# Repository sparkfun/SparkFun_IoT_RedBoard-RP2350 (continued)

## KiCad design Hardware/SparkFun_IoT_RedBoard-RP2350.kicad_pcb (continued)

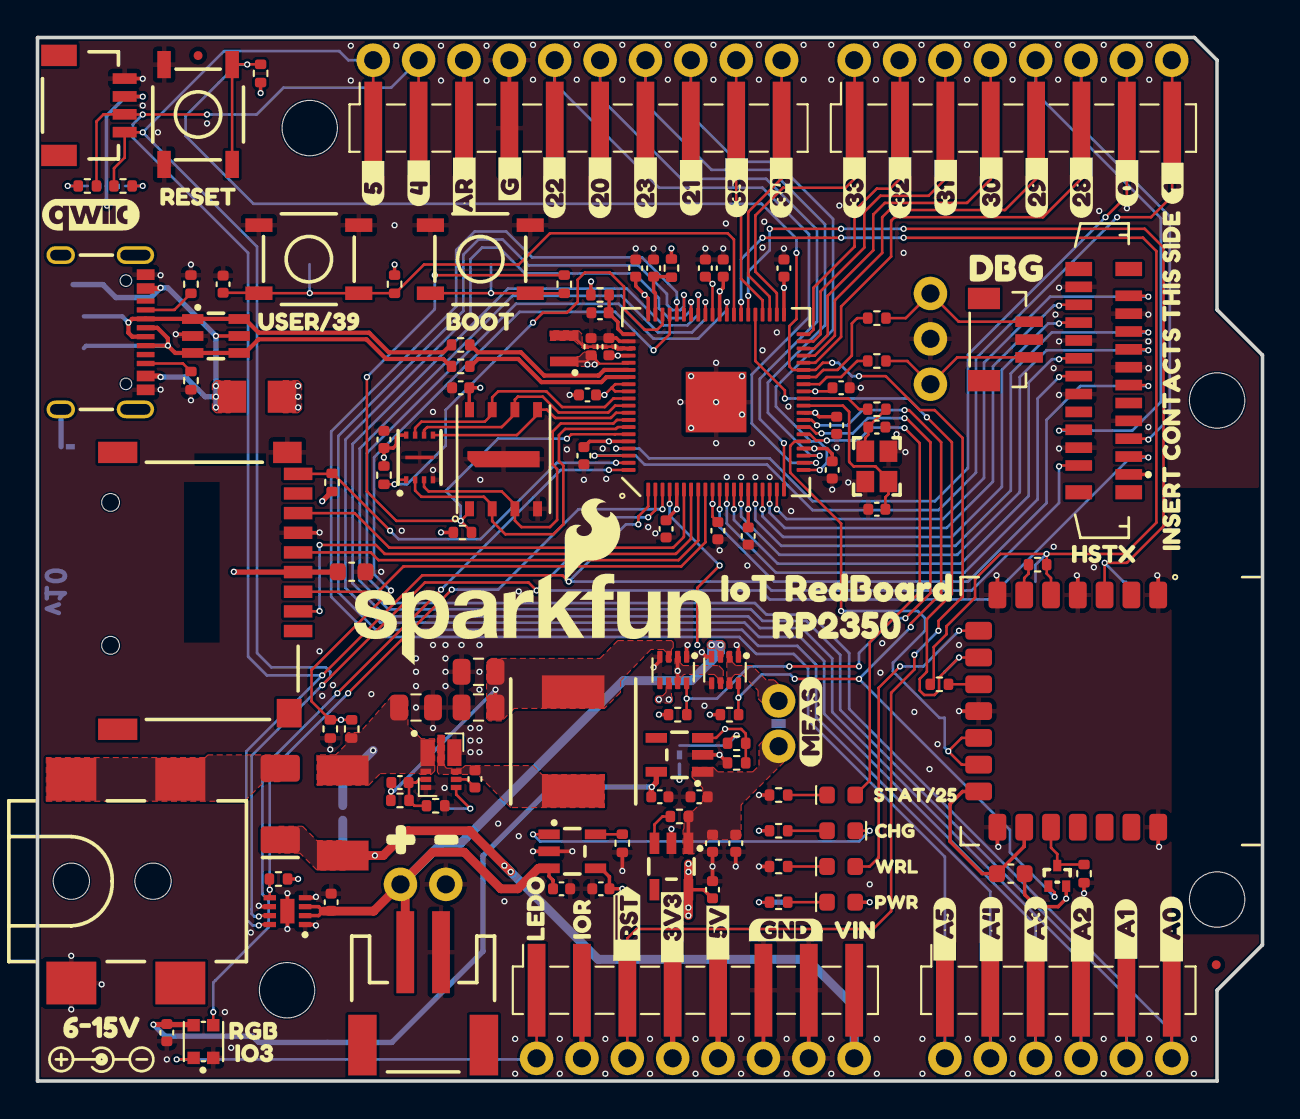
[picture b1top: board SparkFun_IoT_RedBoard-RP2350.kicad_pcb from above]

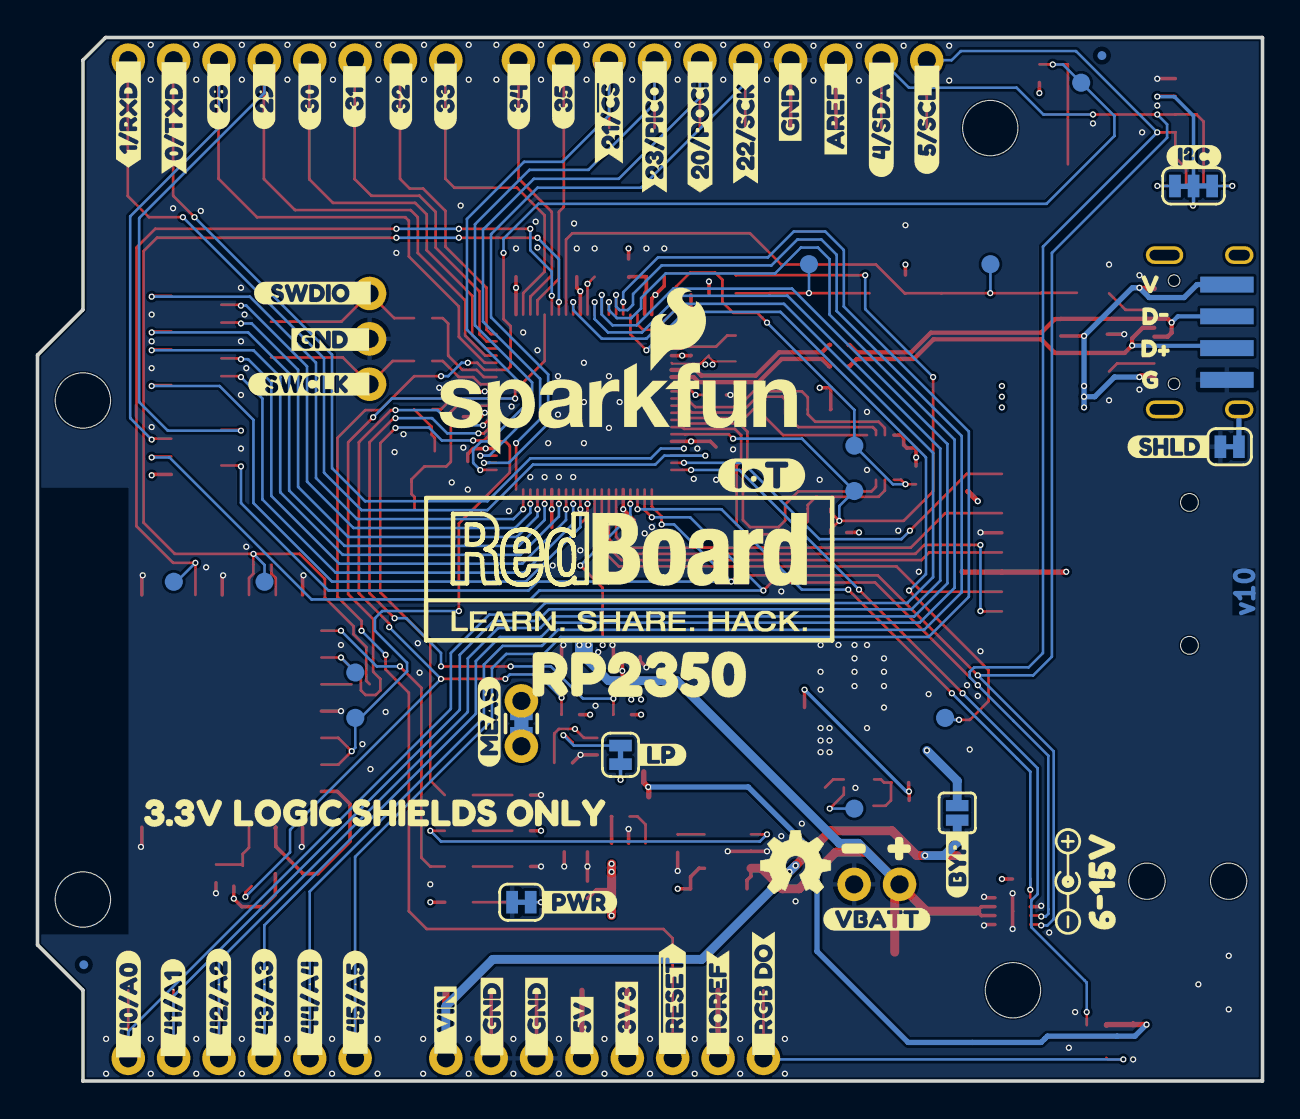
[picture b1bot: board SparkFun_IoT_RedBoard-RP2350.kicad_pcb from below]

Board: 4 copper layers, 68.6 x 58.4 mm, 244 parts (74 on the bottom side), 108 nets.

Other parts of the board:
Ref**: Val**; POLARITY_MARKING_CENTER_POSITIVE
Ref**#2: Val**; OSHW_Logo_4mm
Ref**#3: Val**; POLARITY_MARKING_CENTER_POSITIVE
kibuzzard-67A3E0D1: G***; kibuzzard-67A3E0D1
kibuzzard-67A3E1A1: G***; kibuzzard-67A3E1A1
kibuzzard-67A3E1A7: G***; kibuzzard-67A3E1A7
kibuzzard-67A3E1AE: G***; kibuzzard-67A3E1AE
kibuzzard-67A3E1B5: G***; kibuzzard-67A3E1B5
kibuzzard-67A3E1BE: G***; kibuzzard-67A3E1BE
kibuzzard-67A3E1C5: G***; kibuzzard-67A3E1C5
kibuzzard-67A3E1CD: G***; kibuzzard-67A3E1CD
kibuzzard-67A3E1E0: G***; kibuzzard-67A3E1E0
kibuzzard-67A3E1FA: G***; kibuzzard-67A3E1FA
kibuzzard-67A3E2A5: G***; kibuzzard-67A3E2A5
kibuzzard-67A3E2C6: G***; kibuzzard-67A3E2C6
kibuzzard-67A3E4A3: G***; kibuzzard-67A3E4A3
kibuzzard-67A3E4D1: G***; kibuzzard-67A3E4D1
kibuzzard-67A3E09E: G***; kibuzzard-67A3E09E
kibuzzard-67A3E12A: G***; kibuzzard-67A3E12A
kibuzzard-67A3E17B: G***; kibuzzard-67A3E17B
kibuzzard-67A3E20D: G***; kibuzzard-67A3E20D
kibuzzard-67A3E24D: G***; kibuzzard-67A3E24D
kibuzzard-67A3E25A: G***; kibuzzard-67A3E25A
kibuzzard-67A3E26A: G***; kibuzzard-67A3E26A
kibuzzard-67A3E43C: G***; kibuzzard-67A3E43C
kibuzzard-67A3E45D: G***; kibuzzard-67A3E45D
kibuzzard-67A3E112: G***; kibuzzard-67A3E112
kibuzzard-67A3E140: G***; kibuzzard-67A3E140
kibuzzard-67A3E168: G***; kibuzzard-67A3E168
kibuzzard-67A3E171: G***; kibuzzard-67A3E171
kibuzzard-67A3E183: G***; kibuzzard-67A3E183
kibuzzard-67A3E201: G***; kibuzzard-67A3E201
kibuzzard-67A3E235: G***; kibuzzard-67A3E235
kibuzzard-67A3E254: G***; kibuzzard-67A3E254
kibuzzard-67A3E263: G***; kibuzzard-67A3E263
kibuzzard-67A3E284: G***; kibuzzard-67A3E284
kibuzzard-67A3E455: G***; kibuzzard-67A3E455
kibuzzard-67A3F3F2: G***; kibuzzard-67A3F3F2
kibuzzard-67A3F4AA: G***; kibuzzard-67A3F4AA
kibuzzard-67A3F4E6: G***; kibuzzard-67A3F4E6
kibuzzard-67A3F5C2: G***; kibuzzard-67A3F5C2
kibuzzard-67A3F5D5: G***; kibuzzard-67A3F5D5
kibuzzard-67A3F5FB: G***; kibuzzard-67A3F5FB
kibuzzard-67A3F6A9: G***; kibuzzard-67A3F6A9
kibuzzard-67A3F6CD: G***; kibuzzard-67A3F6CD
kibuzzard-67A3F6E9: G***; kibuzzard-67A3F6E9
kibuzzard-67A3F7A5: G***; kibuzzard-67A3F7A5
kibuzzard-67A3F7B2: G***; kibuzzard-67A3F7B2
kibuzzard-67A3F7C3: G***; kibuzzard-67A3F7C3
kibuzzard-67A3F7D3: G***; kibuzzard-67A3F7D3
kibuzzard-67A3F9C4: G***; kibuzzard-67A3F9C4
kibuzzard-67A3F9DC: G***; kibuzzard-67A3F9DC
kibuzzard-67A3F59C: G***; kibuzzard-67A3F59C
kibuzzard-67A3F62C: G***; kibuzzard-67A3F62C
kibuzzard-67A3F63E: G***; kibuzzard-67A3F63E
kibuzzard-67A3F64D: G***; kibuzzard-67A3F64D
kibuzzard-67A3F71F: G***; kibuzzard-67A3F71F
kibuzzard-67A3F72C: G***; kibuzzard-67A3F72C
kibuzzard-67A3F73E: G***; kibuzzard-67A3F73E
kibuzzard-67A3F74E: G***; kibuzzard-67A3F74E
kibuzzard-67A3F78A: G***; kibuzzard-67A3F78A
kibuzzard-67A3F532: G***; kibuzzard-67A3F532
kibuzzard-67A3F552: G***; kibuzzard-67A3F552
kibuzzard-67A3F565: G***; kibuzzard-67A3F565
kibuzzard-67A3F577: G***; kibuzzard-67A3F577
kibuzzard-67A3F625: G***; kibuzzard-67A3F625
kibuzzard-67A3F633: G***; kibuzzard-67A3F633
kibuzzard-67A3F639: G***; kibuzzard-67A3F639
kibuzzard-67A3F646: G***; kibuzzard-67A3F646
kibuzzard-67A3F657: G***; kibuzzard-67A3F657
kibuzzard-67A3F666: G***; kibuzzard-67A3F666
kibuzzard-67A3F682: G***; kibuzzard-67A3F682
kibuzzard-67A3F699: G***; kibuzzard-67A3F699
kibuzzard-67A3F769: G***; kibuzzard-67A3F769
kibuzzard-67A3F773: G***; kibuzzard-67A3F773
kibuzzard-67A3F799: G***; kibuzzard-67A3F799
kibuzzard-67A657F3: G***; kibuzzard-67A657F3
kibuzzard-67A657FD: G***; kibuzzard-67A657FD
kibuzzard-6761DE89: G***; kibuzzard-6761DE89
kibuzzard-6761DE91: G***; kibuzzard-6761DE91
kibuzzard-6765AF34: G***; kibuzzard-6765AF34
kibuzzard-6765AF51: G***; kibuzzard-6765AF51
kibuzzard-6765B674: G***; kibuzzard-6765B674
kibuzzard-67608A8F: G***; kibuzzard-67608A8F
kibuzzard-67608A60: G***; kibuzzard-67608A60
kibuzzard-67608A88: G***; kibuzzard-67608A88
kibuzzard-67608AA5: G***; kibuzzard-67608AA5
kibuzzard-67608E95: G***; kibuzzard-67608E95
kibuzzard-67608F94: G***; kibuzzard-67608F94
kibuzzard-675766BF: G***; kibuzzard-675766BF
kibuzzard-676080F0: G***; kibuzzard-676080F0
kibuzzard-676083AD, kibuzzard-676083AD#2: G***; kibuzzard-676083AD
kibuzzard-676084E8: G***; kibuzzard-676084E8
kibuzzard-676098CD: G***; kibuzzard-676098CD
kibuzzard-6760897E: G***; kibuzzard-6760897E
kibuzzard-67576710: G***; kibuzzard-67576710
kibuzzard-67576718: G***; kibuzzard-67576718
kibuzzard-67608476: G***; kibuzzard-67608476
kibuzzard-67608507: G***; kibuzzard-67608507
kibuzzard-67608599: G***; kibuzzard-67608599
kibuzzard-67608612: G***; kibuzzard-67608612
kibuzzard-67608662: G***; kibuzzard-67608662
kibuzzard-67608910: G***; kibuzzard-67608910

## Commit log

2024-12-16 v01 ready for review
2024-12-17 Update v01 from checklist. Added measures.
2024-12-18 Update parts with 3D models.
2024-12-20 v01 post design review changes. Panelize/CAM.
    Remove F3.
    Added switched power for qwiic, rgb, sd.
    Update USB diode for prod friendly package.
    Added debounce cap on User button.
    Swap user and boot buttons.
    Make F2 a smaller package.
2025-02-06 Update for reds
    Change version number to v10.
    Make user button number correct.
    Rotate HSTX conn 180 degrees electrically.
    Add silk for HSTX contact direction.
    Increase silk text size where it made sense.
    Increase silk label length on PTHs.
2025-02-07 Update post reds review
    Added SOT489
    Move vias around so they don't interfere with silk
    Change Barrel Jack voltage range.
    Increase VUSB trace width.
    Add silk to HSTX connector.
    Panelize & CAM.
2025-02-13 Updated top paste layer
2025-02-14 Initial docs commit
    Adding background files for GH pages along with initial documentation page content.
2025-02-20 Docs Update
    Minor docs update for Quickstart & other sections.
2025-02-27 Minor docs update
    Adding initial UF2 page & minor changes to existing files.
2025-03-10 Add Arduino Network demo.
2025-03-10 Add MPY Network demo.
2025-03-10 Docs update
    Adding photos & minor edits to quick start, intro & hardware overview.
2025-03-11 simple banner for the repo - new style - testing
2025-03-13 Docs Initial Review
    Initial review of docs update. Minor edits to existing .md files & adding board files to assets folder.
2025-03-13 Documentation Initial Review
    Initial review changes for docs. Adding workflows files to publish site.
2025-03-13 Deployed 0c276f3 with MkDocs version: 1.6.1
2025-03-13 Update introduction.md
    Fixing banner image link
2025-03-13 Deployed fd5eea8 with MkDocs version: 1.6.1
2025-03-13 Update README.md
    Updating README.md from template.
2025-03-13 Deployed 900e21f with MkDocs version: 1.6.1
2025-03-17 Update Quick Start
    Adding Arduino code snippets.
2025-03-17 Deployed 1c78118 with MkDocs version: 1.6.1
2025-03-17 Update README.md
    Fix hyperlink typo.
2025-03-17 Deployed 0b20c9d with MkDocs version: 1.6.1
2025-03-20 Minor Docs Update
    Re-uploading schematic & fixing datasheet typo.
2025-03-20 Deployed 2e6dd61 with MkDocs version: 1.6.1
2025-03-20 Schematic link fix
    Updating schematic filename to properly update.
2025-03-20 Deployed 72cd542 with MkDocs version: 1.6.1
2025-03-20 Update mkdocs.yml
    Removing unnecessary Hardware Assembly nav item.
2025-03-20 Deployed f01e701 with MkDocs version: 1.6.1
2025-05-01 Update hardware_overview.md
    Fixing typo for RP2350 chip variant.
2025-05-01 Deployed 8fa2269 with MkDocs version: 1.6.1
2025-10-07 Replace <center> tags
    Updated documentation to use <article> and <figure> tags with markdown attributes for centered content, replacing deprecated <center> tags for improved semantic structure and compatibility.
2025-10-07 Add datasheet for PSRAM
    Fixes broken link
2025-10-07 Removed git-authors plugin
    Removed git-authors plugin as part of documentation standardization
2025-10-07 Update mkdocs.yml
    Update emoji plugin
2025-10-08 Deployed a2c9e02 with MkDocs version: 1.6.1
2026-06-03 Deployed 46926c4 with MkDocs version: 1.6.1
